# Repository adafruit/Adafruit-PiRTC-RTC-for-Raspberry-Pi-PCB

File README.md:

## Adafruit PiRTC RTC for Raspberry Pi PCB

<a href="http://www.adafruit.com/products/3386"><br/>
Click here to purchase one from the Adafruit shop</a>

PCB files for the Adafruit PiRTC RTC for Raspberry Pi. Format is EagleCAD schematic and board layout

For more details, check out the product page at
* http://www.adafruit.com/product/3386

### Description

This is a great battery-backed real time clock (RTC) that allows your Raspberry Pi project to keep track of time if the power is lost. Perfect for data-logging, clock-building, time-stamping, timers and alarms, etc. Equipped with PCF8523 RTC, it works great with the Raspberry Pi and has native kernel support.

Works perfectly with any Raspberry Pi (or similar single board linux computer) including the Pi 1, Pi 2, Pi 3, Pi Zero, A+, B+ etc.

Fully assembled & tested PCB plugs directly into your Pi's GPIO pins - No soldering required!
Will keep time for 5 years or more

**Note: This product does not come with a CR1220 coin cell battery.**

### License

Adafruit invests time and resources providing this open source design, please support Adafruit and open-source hardware by purchasing products from [Adafruit](https://www.adafruit.com)!

Designed by Limor Fried/Ladyada for Adafruit Industries.

Creative Commons Attribution/Share-Alike, all text above must be included in any redistribution. See license.txt for additional details.

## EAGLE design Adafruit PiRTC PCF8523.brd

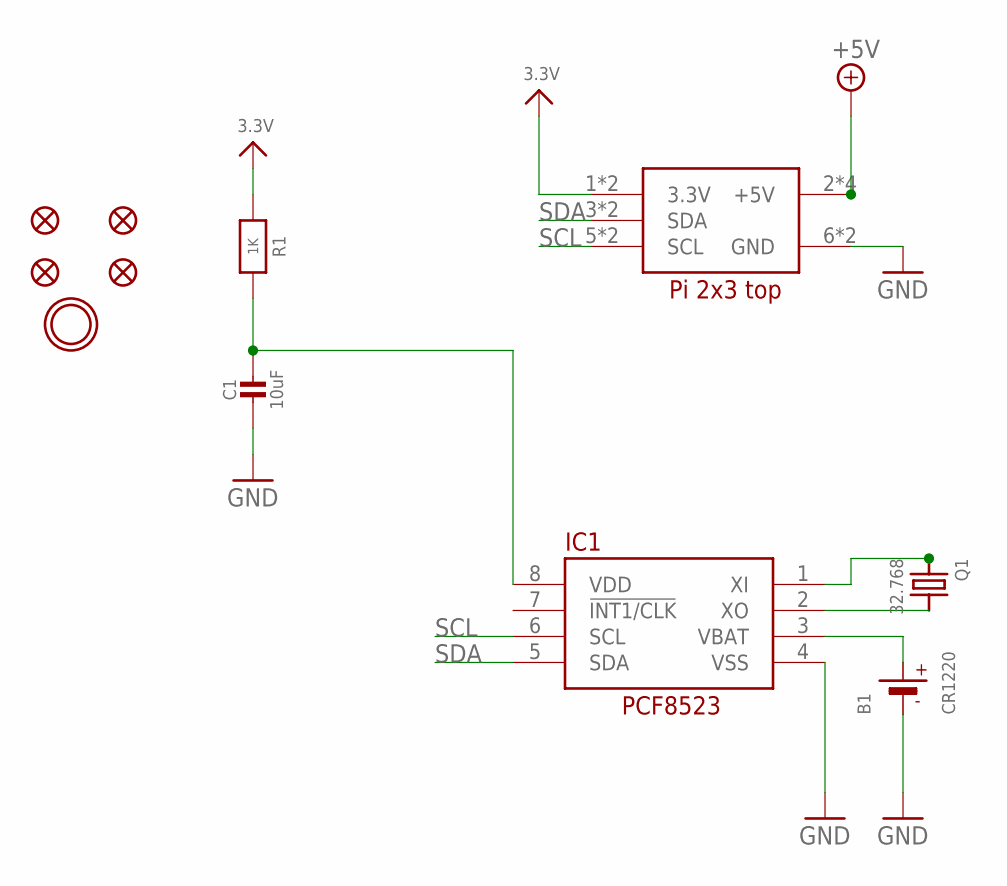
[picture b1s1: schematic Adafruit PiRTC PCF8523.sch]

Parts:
B1: CR1220
C1: 10uF; 0805-NO
FID1, FID2, FID3, FID4: FIDUCIAL_1MM
IC1: RTC_PCF8523T; SOIC8_150MIL
Q1: 32.768; CRYSTAL_8X3.8
R1: 1K; 0805-NO
RPI1: RASPBERRYPI_2X3; RASPBERRYPI_2X3_THMSMT
U$4: MOUNTINGHOLE3.0THIN; MOUNTINGHOLE_3.0_PLATEDTHIN

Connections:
3.3V: R1.1, RPI1.1 (3.3V), RPI1.1' (3.3V)
+5V: RPI1.2 (+5V), RPI1.2' (+5V), RPI1.4 (+5V), RPI1.4' (+5V)
GND: B1.-, C1.2, IC1.4 (VSS), RPI1.6 (GND), RPI1.6' (GND)
unnamed: IC1.1 (XI), Q1.P$1 (1)
unnamed: IC1.2 (XO), Q1.P$4 (2)
SCL: IC1.6 (SCL), RPI1.5 (SCL), RPI1.5' (SCL)
SDA: IC1.5 (SDA), RPI1.3 (SDA), RPI1.3' (SDA)
VBAT: B1.+$1 (+), B1.+$2 (+), IC1.3 (VBAT)
VDD: C1.1, IC1.8 (VDD), R1.2

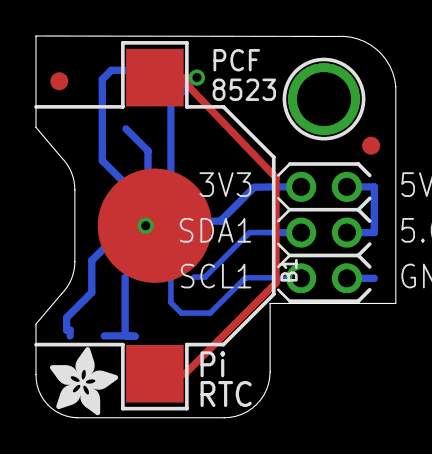
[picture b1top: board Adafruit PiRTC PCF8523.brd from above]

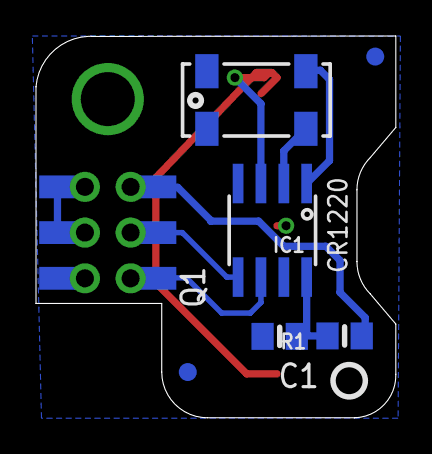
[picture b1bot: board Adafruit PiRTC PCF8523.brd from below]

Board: 2 copper layers, 20.0 x 21.2 mm, 13 parts (7 on the bottom side), 9 nets.

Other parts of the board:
U$2: ADAFRUIT_3.5MM
U$3: PCBFEAT-REV-040

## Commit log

2017-06-14 init!

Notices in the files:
parts and their libraries:
microbuilder: This work is placed in the public domain, and may be freely used for commercial and non-commercial work with the following conditions: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
